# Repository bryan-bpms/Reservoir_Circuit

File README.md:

# ECE 298 Reservoir Circuit Designs
ECE 298 Reservoir Circuit Schematic and PCB Design, modeled in KiCad. No longer maintained.

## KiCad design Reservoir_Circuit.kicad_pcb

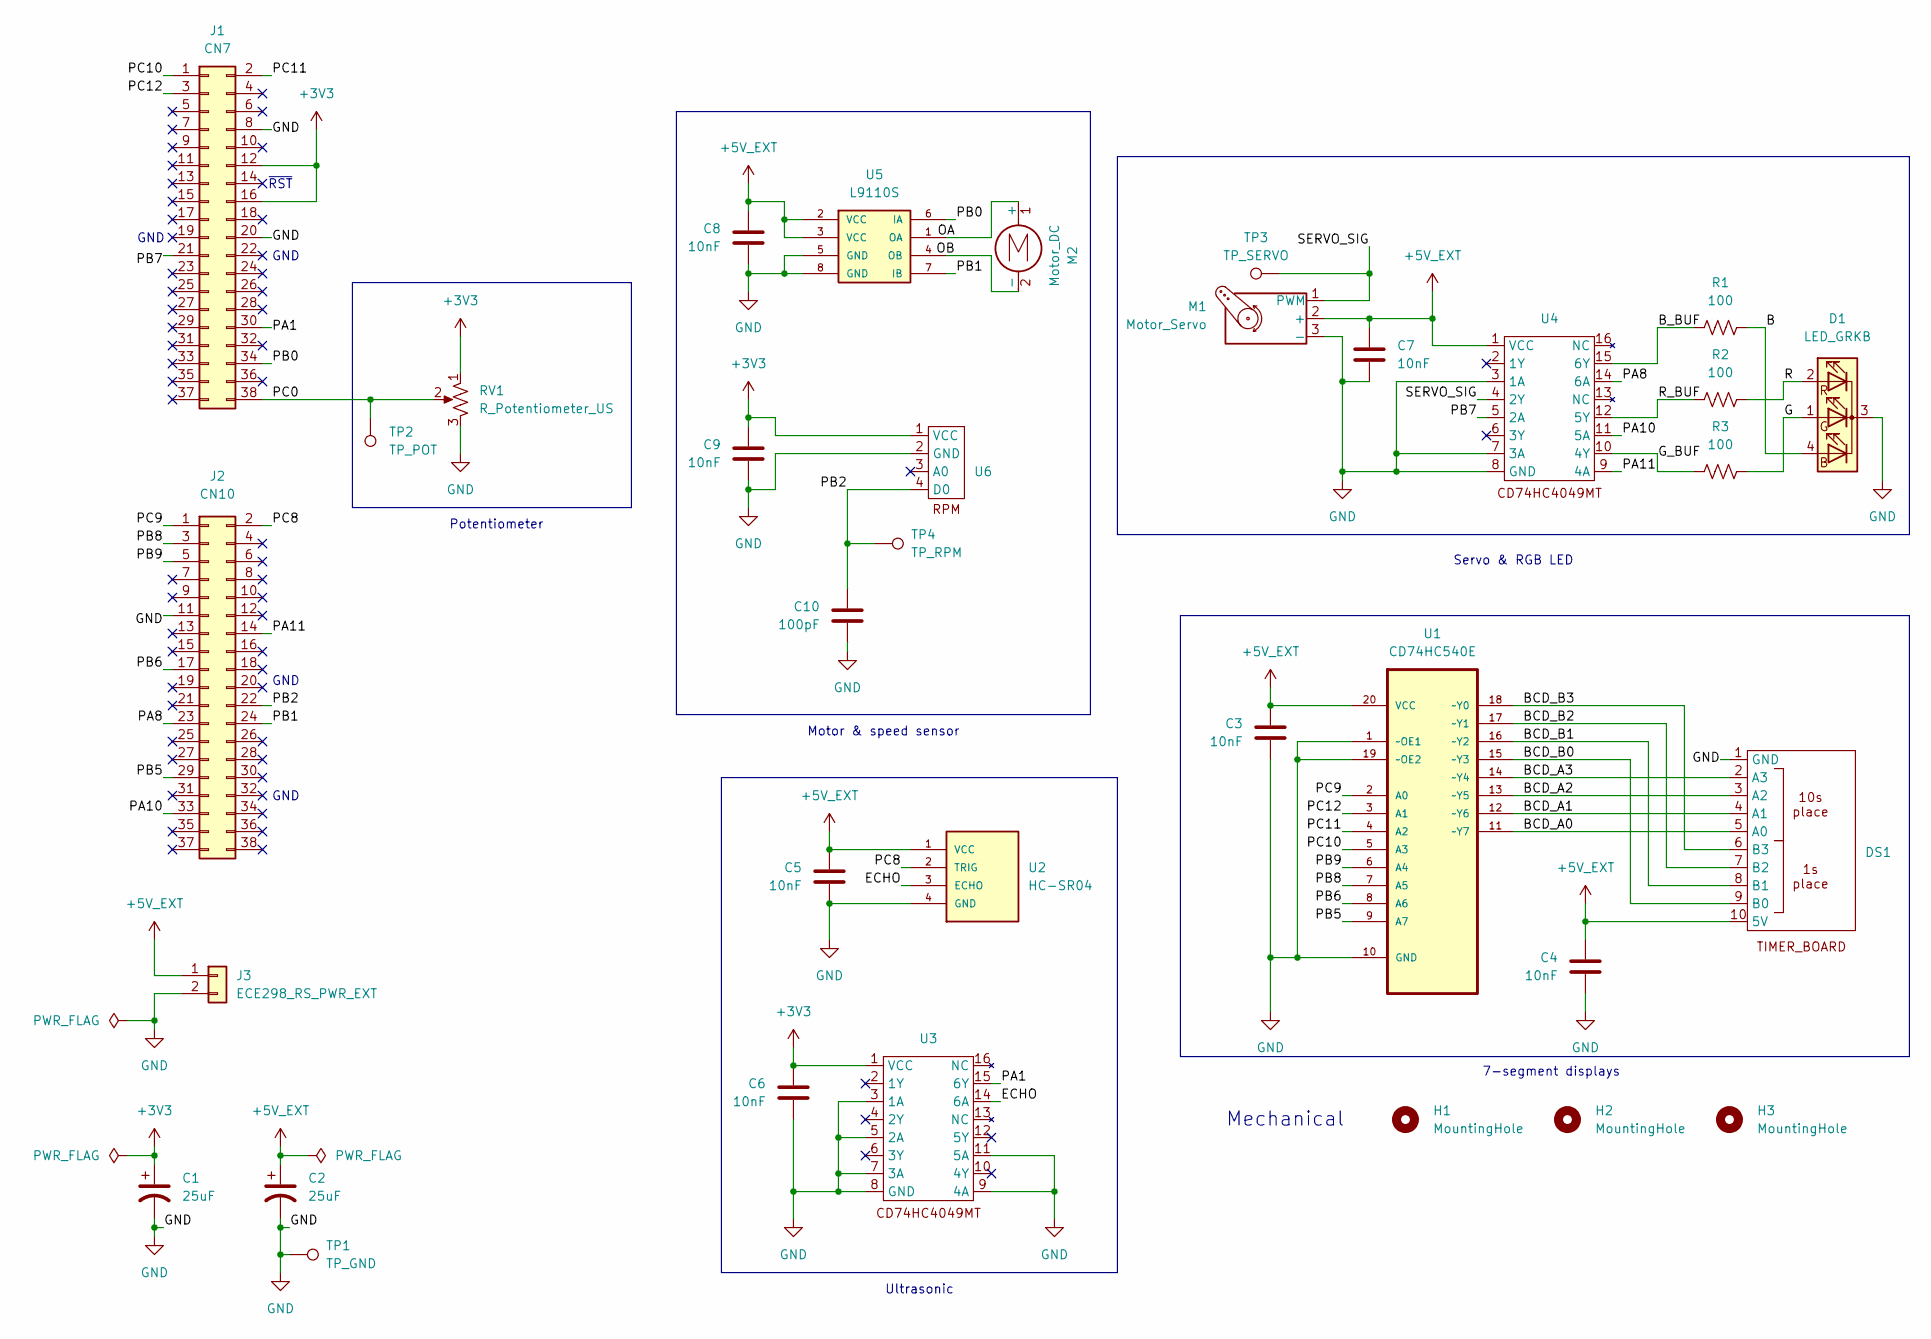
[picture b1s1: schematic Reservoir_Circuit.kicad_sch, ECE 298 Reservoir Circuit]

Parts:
C1, C2: 25uF; C_Elec_3x5.4
C3, C4, C5, C6, C7, C8, C9: 10nF; C_1206_3216Metric
C10: 100pF; C_1206_3216Metric
D1: LED_GRKB; LED_Inolux_IN-PI554FCH_PLCC4_5.0x5.0mm_P3.2mm
DS1: PinHeader_1x10_P2.54mm_Vertical
H1, H2, H3: MountingHole; MountingHole_3.2mm_M3
J1: CN7; PinSocket_2x19_P2.54mm_Vertical
J2: CN10; PinSocket_2x19_P2.54mm_Vertical
J3: ECE298_RS_PWR_EXT; JST_EH_B2B-EH-A_1x02_P2.50mm_Vertical
M1: Motor_Servo; PinHeader_1x03_P2.54mm_Vertical
M2: Motor_DC; PinHeader_1x02_P2.54mm_Vertical
R1, R2, R3: 100; R_0603_1608Metric
RV1: R_Potentiometer_US; Potentiometer_Bourns_3314J_Vertical
TP1: TP_GND; PinHeader_1x01_P1.00mm_Vertical
TP2: TP_POT; PinHeader_1x01_P1.00mm_Vertical
TP3: TP_SERVO; PinHeader_1x01_P1.00mm_Vertical
TP4: TP_RPM; PinHeader_1x01_P1.00mm_Vertical
U1: CD74HC540E; SOIC127P1030X265-20N; MPN CD74HC540E
U2: HC-SR04; XCVR_HC-SR04
U3, U4: SOIC127P600X175-16N
U5: L9110S; SOIC127P599X172-8N; PARTREV NA
U6: PinHeader_1x04_P2.54mm_Vertical

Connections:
+3V3: C1.1, C6.1, C9.1, J1.12, J1.16, RV1.1, U3.1 (VCC), U6.1 (VCC)
+5V_EXT: C2.1, C3.1, C4.1, C5.1, C7.1, C8.1, DS1.10 (5V), J3.1, M1.2 (+), U1.20 (VCC), U2.1 (VCC), U4.1 (VCC), U5.2 (VCC), U5.3 (VCC)
/B: D1.4 (BA), R1.1
/BCD_A0: DS1.5 (A0), U1.11 (~Y7)
/BCD_A1: DS1.4 (A1), U1.12 (~Y6)
/BCD_A2: DS1.3 (A2), U1.13 (~Y5)
/BCD_A3: DS1.2 (A3), U1.14 (~Y4)
/BCD_B0: DS1.9 (B0), U1.15 (~Y3)
/BCD_B1: DS1.8 (B1), U1.16 (~Y2)
/BCD_B2: DS1.7 (B2), U1.17 (~Y1)
/BCD_B3: DS1.6 (B3), U1.18 (~Y0)
/B_BUF: R1.2, U4.15 (6Y)
/ECHO: U2.3 (ECHO), U3.14 (6A)
/G: D1.1 (GA), R3.1
/G_BUF: R3.2, U4.10 (4Y)
/OA: M2.1 (+), U5.1 (OA)
/OB: M2.2 (-), U5.4 (OB)
/PA1: J1.30, U3.15 (6Y)
/PA8: J2.23, U4.14 (6A)
/PA10: J2.33, U4.11 (5A)
/PA11: J2.14, U4.9 (4A)
/PB0: J1.34, U5.6 (IA)
/PB1: J2.24, U5.7 (IB)
/PB2: C10.1, J2.22, TP4.1 (1_1), U6.4 (D0)
/PB5: J2.29, U1.9 (A7)
/PB6: J2.17, U1.8 (A6)
/PB7: J1.21, U4.5 (2A)
/PB8: J2.3, U1.7 (A5)
/PB9: J2.5, U1.6 (A4)
/PC0: J1.38, RV1.2, TP2.1 (1_1)
/PC8: J2.2, U2.2 (TRIG)
/PC9: J2.1, U1.2 (A0)
/PC10: J1.1, U1.5 (A3)
/PC11: J1.2, U1.4 (A2)
/PC12: J1.3, U1.3 (A1)
/R: D1.2 (RA), R2.1
/R_BUF: R2.2, U4.12 (5Y)
/SERVO_SIG: M1.1 (PWM), TP3.1 (1_1), U4.4 (2Y)
GND: C1.2, C2.2, C3.2, C4.2, C5.2, C6.2, C7.2, C8.2, C9.2, C10.2, D1.3 (K), DS1.1 (GND), J1.8, J1.20, J2.11, J3.2, M1.3 (-), RV1.3, TP1.1 (1_1), U1.1 (~OE1), U1.10 (GND), U1.19 (~OE2), U2.4 (GND), U3.3 (1A), U3.5 (2A), U3.7 (3A), U3.8 (GND), U3.9 (4A), U3.11 (5A), U4.3 (1A), U4.7 (3A), U4.8 (GND), U5.5 (GND), U5.8 (GND), U6.2 (GND)

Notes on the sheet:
Motor & speed sensor
Servo & RGB LED
Potentiometer
Mechanical
GND
~{RST}
Ultrasonic
7-segment displays

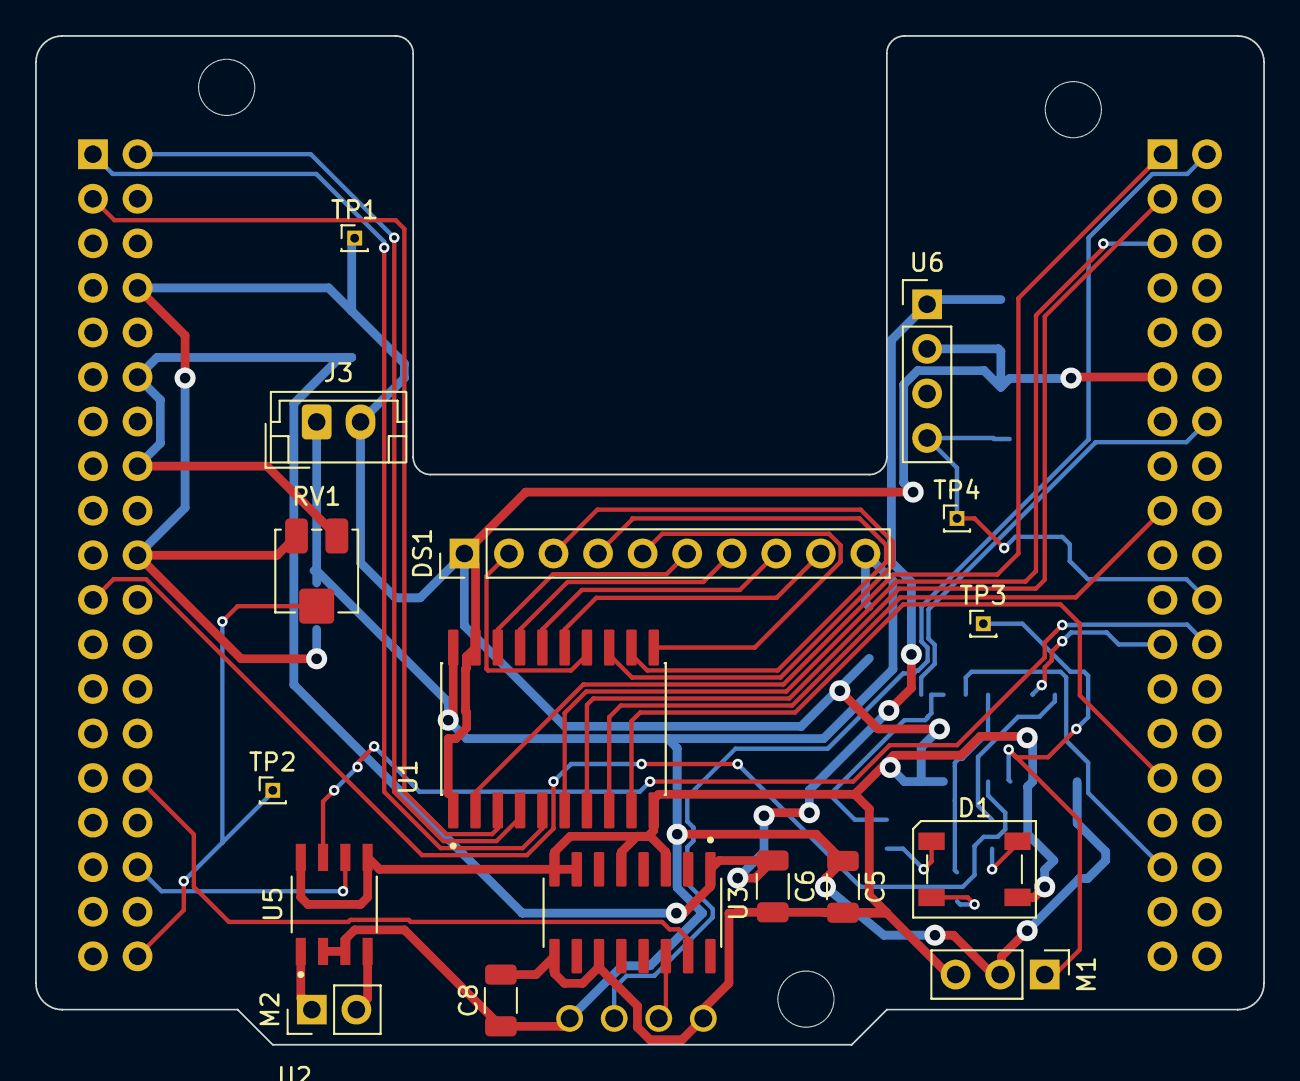
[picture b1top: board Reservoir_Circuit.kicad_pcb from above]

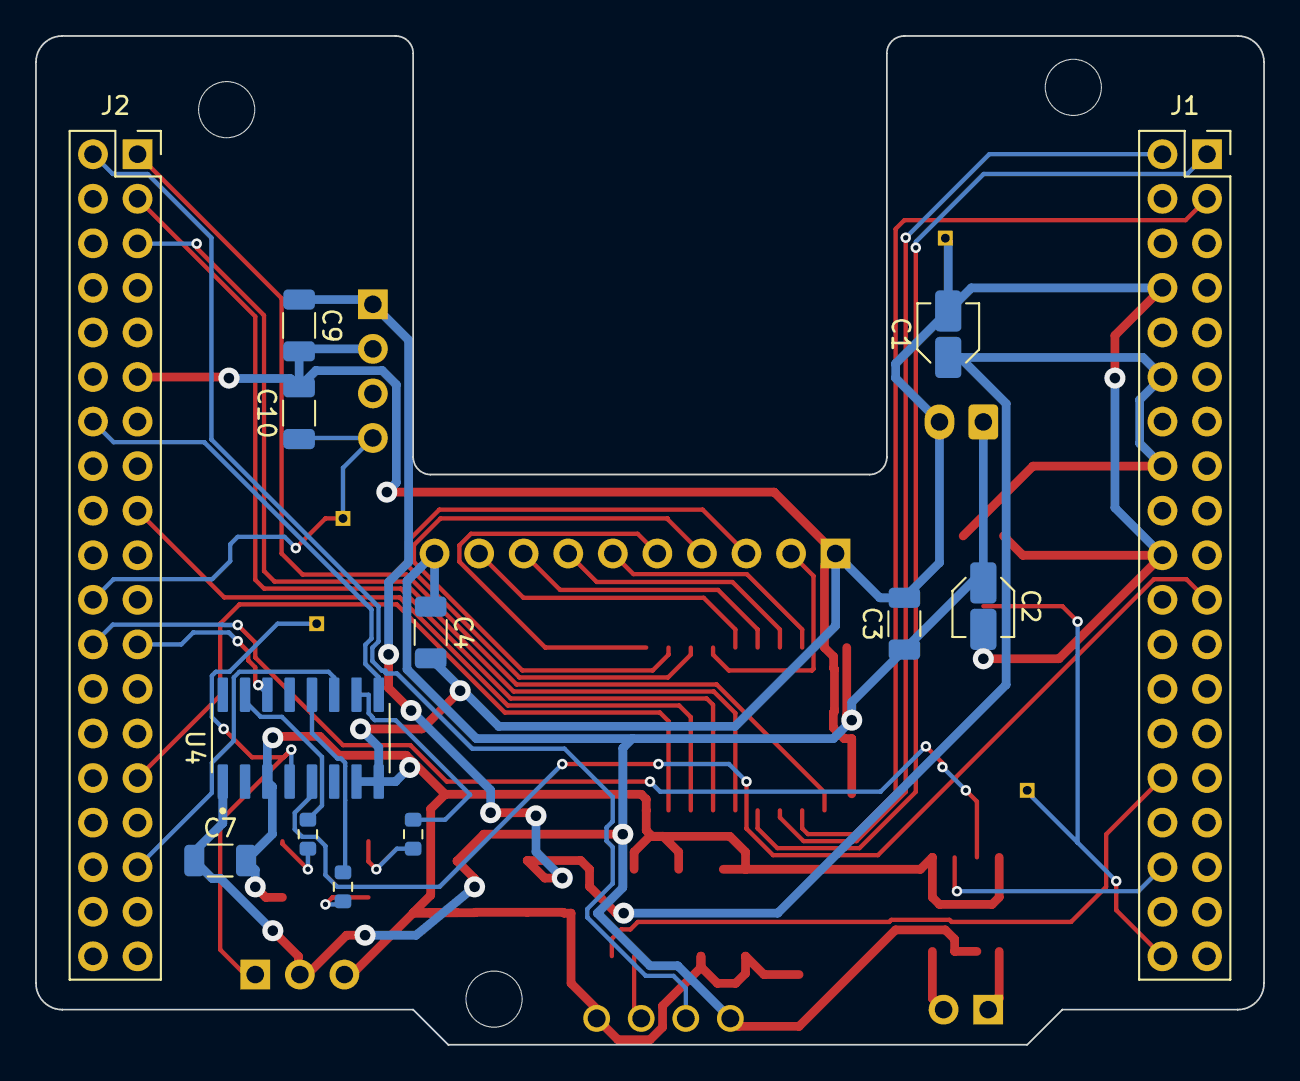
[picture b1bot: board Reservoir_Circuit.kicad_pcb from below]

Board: 2 copper layers, 70.0 x 57.5 mm, 34 parts (13 on the bottom side), 39 nets.
